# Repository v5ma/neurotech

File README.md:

Wiki
====

https://www.noisebridge.net/wiki/DreamTeam/Brainduinov2

Commands
========

Commands are sent by write ASCII characters to the bluetooth serial device. The brainduino echos back the lower-case compliment of the command sent 15 times followed by a return carridge. For example:

```
Client writes 'S' to bluetooth serial device
If the command is recieved by the brainduino, the brainduino writes 'sssssssssssssss' + '\r' back over bluetooth

```
ASCII | Result
---   | ---
I     | Bypass the MAX7480 (8th-order butterworth filter)
P     | Set 200HZ low-pass corner frequency of MAX7480 (8th-order butterworth filter)
O     | Set 150HZ low-pass corner frequency of MAX7480 (8th-order butterworth filter)
Q     | Set 100HZ low-pass corner frequency of MAX7480 (8th-order butterworth filter)
Z     | Set 50HZ low-pass corner frequency of MAX7480 (8th-order butterworth filter)
M     | Set 40HZ low-pass corner frequency of MAX7480 (8th-order butterworth filter)
S     | Set 32HZ low-pass corner frequency of MAX7480 (8th-order butterworth filter)
V     | Set sample rate to 500HZ
W     | Set sample rate to 250HZ
B     | Set sample rate to 190HZ
A     | Impedance check on with +1ch
T     | Impedance check on with -1ch
C     | Impedance check on with +2ch
D     | Impedance check on with -2ch
E     | Impedance check off
F     | Generate test signal with frequency = 12HZ
G     | Generate test signal with frequency = 28HZ
H     | Generate test signal with frequency = 111HZ
J     | Generate test signal with power = 0.1
K     | Generate test signal with power = 1
Y     | Set 4 channel mode
X     | Set 2 channel mode with 500HZ sample rate
U     | Set 2 channel mode with 250HZ sample rate

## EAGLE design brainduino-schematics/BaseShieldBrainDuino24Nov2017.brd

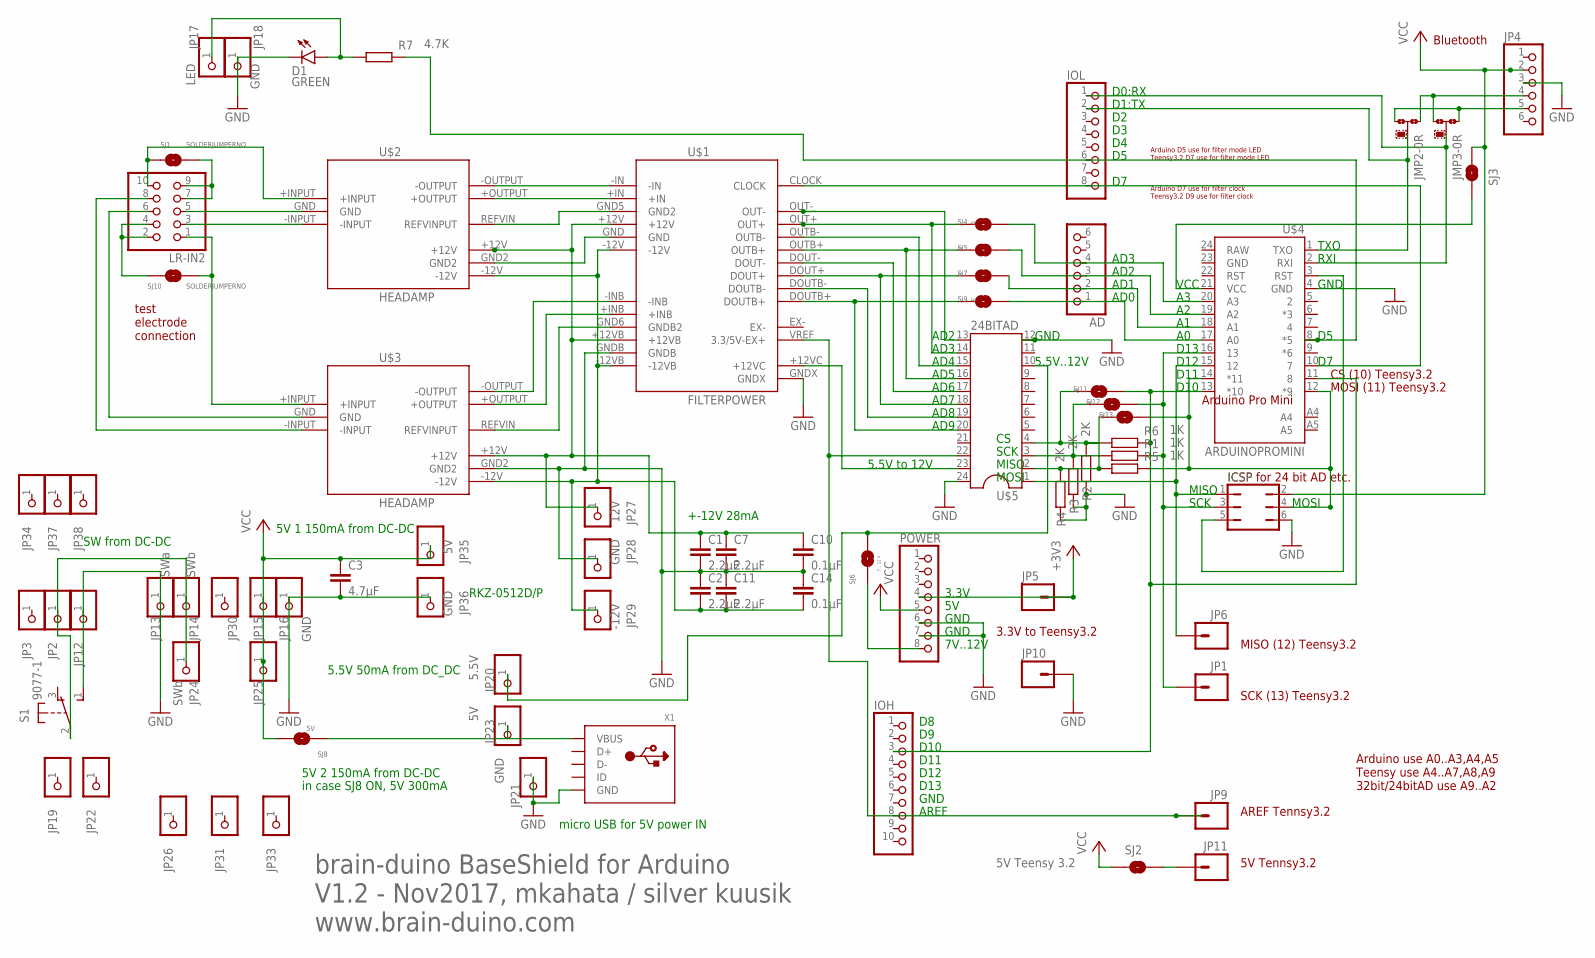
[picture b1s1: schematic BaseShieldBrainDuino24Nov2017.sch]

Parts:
AD: PINHD-1X6; 1X06
C1, C2, C7, C11: 2.2µF; C0402
C3: 4.7µF; C0402
C10, C14: 0.1µF; C0402
D1: GREEN; LED-0603
ICSP: JP3Q
IOH: PINHD-1X10; 1X10
IOL: PINHD-1X8; 1X08
JMP2: RX; A0R-JMP
JMP3: TX; A0R-JMP
JP1, JP5, JP6, JP9, JP10, JP11: M01PTH; 1X01
JP2, JP3, JP12, JP19, JP22, JP26, JP30, JP31, JP33, JP34, JP37, JP38: PINHD-1X1; 1X01
JP4: PINHD-1X6; 1X06
JP13: SWa; 1X01
JP14, JP24: SWb; 1X01
JP15, JP25: +5V; 1X01
JP16, JP18, JP21, JP28, JP36: GND; 1X01
JP17: LED; 1X01
JP20: 5.5V; 1X01
JP23, JP35: 5V; 1X01
JP27: 12V; 1X01
JP29: -12V; 1X01
LR-IN2: PINHD-2X5/90; 2X05/90
POWER: PINHD-1X8; 1X08
R1, R5, R6: 1K; R0402
R2, R3, R4: 2K; R0402
R7: 4.7K; R0402
S1: 9077-1
SJ1, SJ10: SOLDERJUMPERNO; SJ_2S-NO
SJ2: 5V Teensy 3.2; SJ_2S-NO
SJ3: 5V Arduino Pro Mini; SJ_2S-NO
SJ4: A5; SJ_2S-NO
SJ5, SJ11, SJ12, SJ13: A4; SJ_2S-NO
SJ6: 7 .. 12 V; SJ_2S-NO
SJ7: A2; SJ_2S-NO
SJ8: 5V; SJ_2S-NO
SJ9: A0; SJ_2S-NO
U$1: FILTERPOWER
U$2, U$3: HEADAMP
U$4: ARDUINOPROMINI
U$5: 24BITAD
X1: USB_MICRO_20329_V2; 4UCONN_20329_V2

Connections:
+3V3: JP5.1, POWER.4
+12VB: C1.1, C7.1, C10.1, JP27.1, U$1.+12V, U$1.+12VB, U$2.+12V, U$3.+12V
-12V: C2.2, C11.2, C14.2, JP29.1, U$1.-12V, U$1.-12VB, U$2.-12V, U$3.-12V
GND: C1.2, C2.1, C3.2, C7.2, C10.2, C11.1, C14.1, D1.C, ICSP.6, JP4.3, JP10.1, JP12.1, JP13.1, JP16.1, JP18.1, JP21.1, JP28.1, JP36.1, POWER.6, POWER.7, R2.1, R3.1, R4.1, S1.1 (S), U$1.GNDB, U$1.GNDX, U$3.GND2, U$4.4 (GND), U$5.12, U$5.24, X1.BASE@1 (GND), X1.BASE@2 (GND), X1.GND, X1.SPRT@1 (GND), X1.SPRT@2 (GND), X1.SPRT@3 (GND), X1.SPRT@4 (GND)
unnamed: SJ3.1, U$4.21 (VCC)
unnamed: U$1.GND, U$2.GND2
unnamed: JP2.1, JP14.1, JP24.1, S1.2
unnamed: POWER.8, SJ6.1
unnamed: ICSP.3, JP1.1, R1.2, SJ12.2, U$4.16 (13)
unnamed: LR-IN2.8, U$3.-INPUT
unnamed: JP23.1, SJ8.1, X1.VBUS
unnamed: U$1.GND6 (GNDB2), U$3.REFVIN (REFVINPUT)
unnamed: U$1.-INB, U$3.-OUTPUT
unnamed: U$1.+INB, U$3.+OUTPUT
unnamed: LR-IN2.3, U$2.-INPUT
unnamed: U$1.OUTB-, U$5.15
unnamed: U$1.+12VC, U$5.23
unnamed: U$1.OUT-, U$5.13
unnamed: JMP2.1, JMP3.3, JP4.4
unnamed: IOL.8, U$1.CLOCK, U$4.10 (7)
unnamed: ICSP.1, JP6.1, U$4.15 (12), U$5.1
unnamed: IOL.2, JMP2.2, U$4.1 (TXO)
unnamed: U$1.-IN, U$2.-OUTPUT
unnamed: IOL.1, JMP3.2, U$4.2 (RXI)
unnamed: IOH.3, R6.2, SJ11.2, U$4.11 (8), U$4.13 (*10)
unnamed: AD.2, SJ7.2, U$4.18 (A1)
unnamed: AD.1, SJ9.2, U$4.17 (A0)
unnamed: ICSP.4, R5.2, SJ13.2, U$4.12 (*9), U$4.14 (*11)
unnamed: JMP2.3, JMP3.1, JP4.5
unnamed: SJ9.1, U$1.DOUTB+, U$5.20
unnamed: JP11.1, SJ2.2
unnamed: JP20.1, SJ6.2, U$5.10
unnamed: U$1.DOUTB-, U$5.19
unnamed: U$1.+IN, U$2.+OUTPUT
unnamed: SJ7.1, U$1.DOUT+, U$5.18
unnamed: U$1.DOUT-, U$5.17
unnamed: IOH.8, JP9.1, U$1.VREF (3.3/5V-EX+), U$5.22
unnamed: AD.4, SJ4.2, U$4.20 (A3)
unnamed: SJ4.1, U$1.OUT+, U$5.14
unnamed: SJ5.1, U$1.OUTB+, U$5.16
unnamed: LR-IN2.1, SJ10.2, U$3.+INPUT
unnamed: LR-IN2.10, SJ1.1, U$2.+INPUT
unnamed: LR-IN2.7, LR-IN2.9, SJ1.2
unnamed: LR-IN2.2, LR-IN2.4, SJ10.1
unnamed: R2.2, R6.1, SJ11.1, U$5.4
unnamed: R1.1, R3.2, SJ12.1, U$5.3
unnamed: R4.2, R5.1, SJ13.1, U$5.2
unnamed: AD.3, SJ5.2, U$4.19 (A2)
unnamed: U$1.GND5 (GND2), U$2.REFVIN (REFVINPUT)
unnamed: LR-IN2.6, U$3.GND
unnamed: ICSP.5, U$4.3 (RST)
unnamed: D1.A, JP17.1, R7.1
unnamed: IOL.6, R7.2, U$4.8 (*5)
unnamed: LR-IN2.5, U$2.GND
VCC: C3.1, ICSP.2, JP4.2, JP15.1, JP25.1, JP35.1, POWER.5, SJ2.1, SJ3.2, SJ8.2

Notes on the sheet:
D0:RX
D1:TX
D13
D12
AREF
GND
AD0
AD1
AD2
AD3
7V..12V
D10
D11
test electrode connection
MOSI (11) Teensy3.2
brain-duino BaseShield for Arduino V1.2 - Nov2017, mkahata / silver kuusik www.brain-duino.com
Bluetooth
MOSI
MISO
SCK
3.3V to Teensy3.2
SCK (13) Teensy3.2
MISO (12) Teensy3.2
ICSP for 24 bit AD etc.
CS (10) Teensy3.2
Arduino use A0..A3,A4,A5 Teensy use A4..A7,A8,A9 32bit/24bitAD use A9..A2
5V Tennsy3.2
Arduino D7 use for filter clock Teensy3.2 D9 use for filter clock
3.3V
AD9
AD8
AD7
AD6
AD5
AD4
5.5V..12V
AREF Tennsy3.2
TXO
RXI
VCC

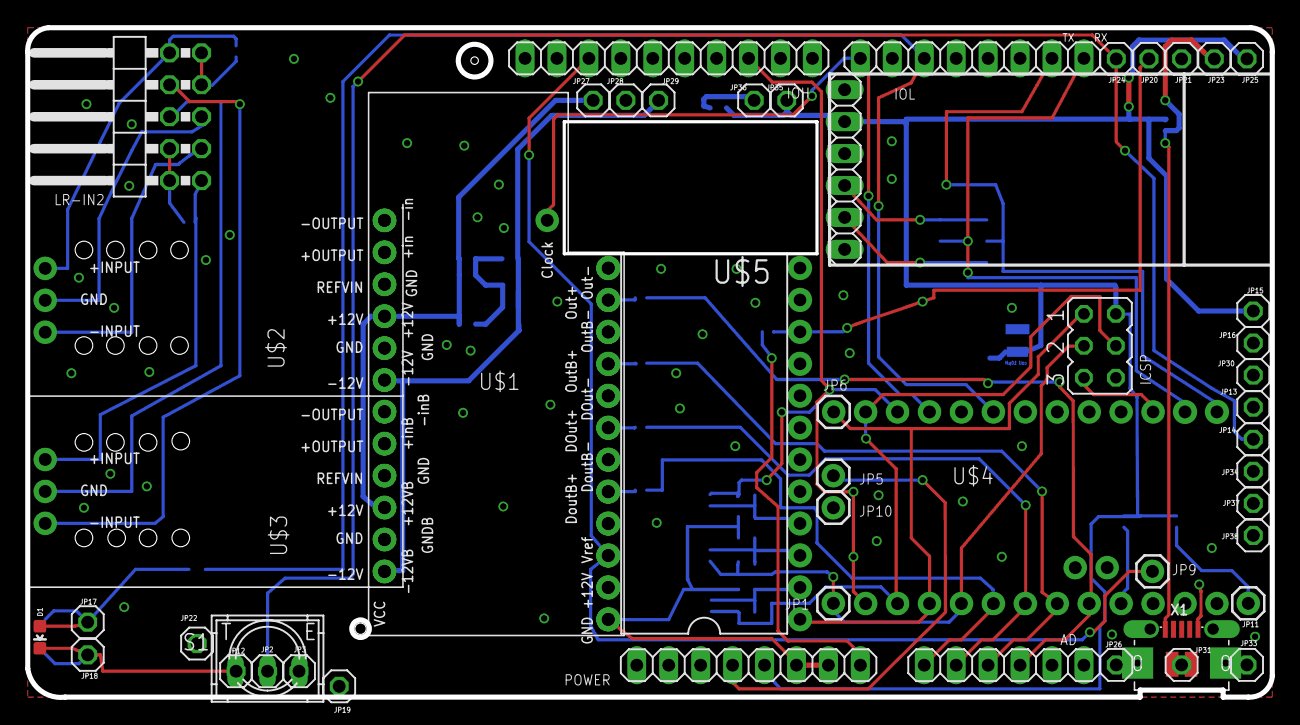
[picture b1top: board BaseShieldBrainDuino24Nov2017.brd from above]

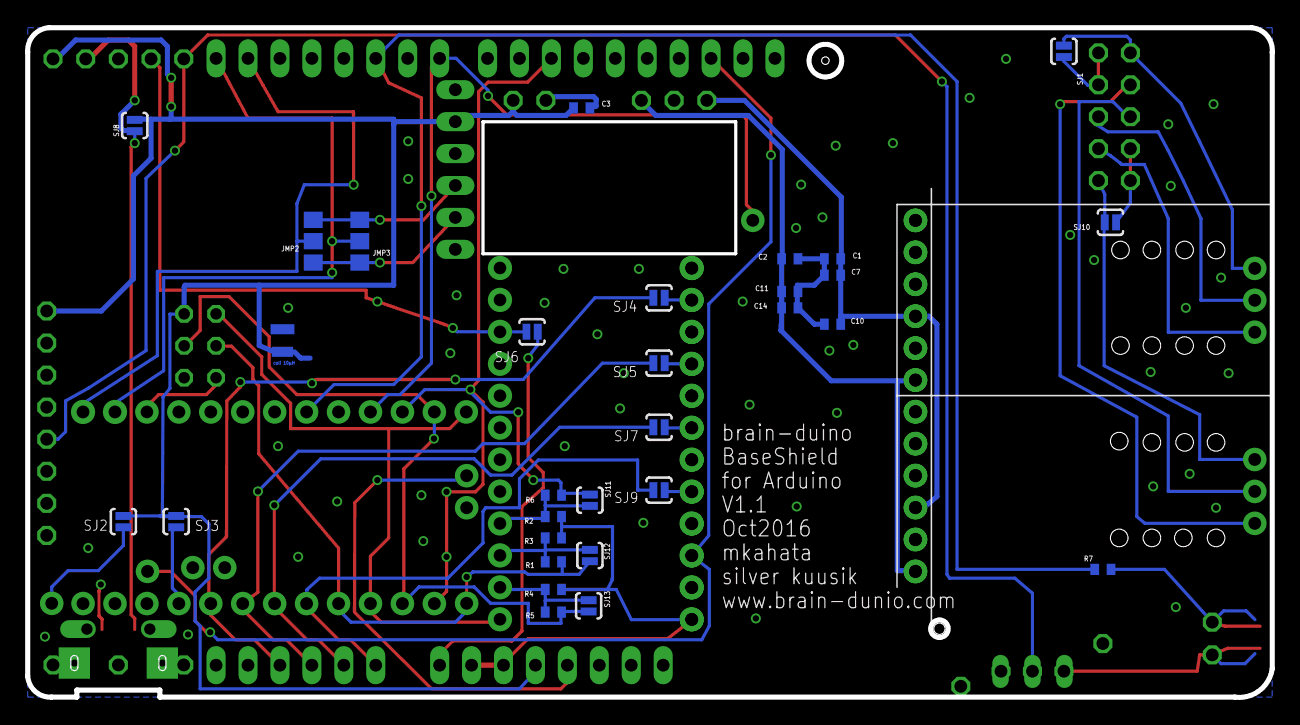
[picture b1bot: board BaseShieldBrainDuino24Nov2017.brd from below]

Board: 2 copper layers, 99.0 x 53.3 mm, 78 parts (29 on the bottom side), 55 nets.

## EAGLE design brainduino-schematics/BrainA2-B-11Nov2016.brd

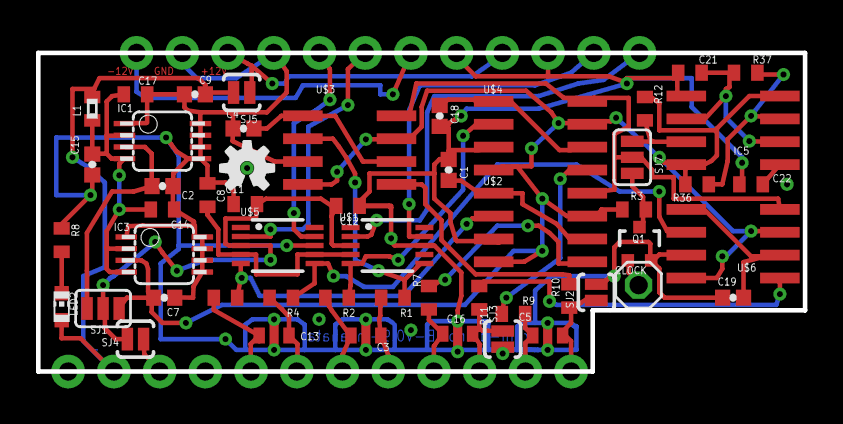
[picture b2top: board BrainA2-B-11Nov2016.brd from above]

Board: 2 copper layers, 42.6 x 17.7 mm, 55 parts (0 on the bottom side), 42 nets.

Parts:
C1, C4, C18, C19: 0.1µF; 0402-CAP
C2, C7: 4.7µF; 0402-CAP
C3, C5, C13, C16: C0603
C8, C11, C12, C14, C17: 2.2uF; C0402
C9, C15: 2.2µF; 0402-CAP
C21: 2.2nF; C0402
C22: 0.1µF; C0402
CLOCK: 1X01
FRAME1: FRAME-LETTER; CREATIVE_COMMONS
IC1: ADP1720ARMZ-3.3; MSOP08
IC3: ADP1720ARMZ-5; MSOP08
IC5: TLC555CDR; SO08
JP1, JP2: 1X12_NO_SILK
L1: BLM15HB121SN1; 0402
LED2: CHIP-LED0603
Q1: MOSFET-NCHANNEL2N7002PW; SOT323
R1, R2, R4, R5: 4.7K; R0402
R3: 10k; R0402
R7, R9, R10, R11: 470; R0402
R8: 20k; R0402
R12: 10K; R0402
R36: 1K; R0402
R37: 100K; R0402
SJ1, SJ7: SJ_3
SJ2, SJ3, SJ4, SJ5: SOLDERJUMPERNO; SJ_2S-NO
U$1, U$5: AD8475; MSOP10
U$2, U$3, U$4, U$6: MAX7480ESA+; MAX7480
U$8: OSHW-LOGO-S

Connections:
5V: C7.1, IC3.3, IC5.4, IC5.8, R3.2, R12.2, R36.2, SJ1.1, U$2.4, U$2.7, U$3.4, U$3.7, U$4.4, U$4.7, U$6.4, U$6.7
+12V: JP2.4, JP2.10, SJ5.1
-12V: JP2.6, JP2.12
GND: C1.1, C2.1, C3.GND, C4.1, C5.GND, C7.2, C8.1, C9.1, C11.1, C12.1, C13.GND, C14.1, C15.1, C16.GND, C17.1, C18.1, C19.1, C21.1, C22.1, IC1.1, IC1.5, IC1.6, IC1.7, IC1.8, IC3.1, IC3.5, IC3.6, IC3.7, IC3.8, IC5.1, JP1.12, JP2.3, JP2.5, JP2.9, JP2.11, Q1.2, R8.2, SJ2.2, SJ3.2, U$1.8, U$2.3, U$3.3, U$4.3, U$5.8, U$6.3
unnamed: C13.2, JP1.8, R5.2
unnamed: C1.2, U$2.1, U$2.6
unnamed: R11.1, U$6.5
unnamed: JP2.1, U$1.2
unnamed: R7.1, U$2.5
unnamed: JP2.2, U$1.9
unnamed: C3.2, JP1.6, R2.2
unnamed: C3.1, JP1.5, R1.2
unnamed: C5.2, JP1.1, R10.2, SJ2.1
unnamed: R2.1, U$1.5, U$4.2
unnamed: C4.2, U$3.1, U$3.6
unnamed: Q1.3, R3.1, SJ7.3
unnamed: JP1.10, SJ4.1
unnamed: R10.1, U$3.5
unnamed: C8.2, U$1.4, U$5.4
unnamed: LED2.C, R8.1
unnamed: R4.1, U$5.6, U$6.2
unnamed: JP2.8, U$5.9
unnamed: C13.1, JP1.7, R4.2
unnamed: JP2.7, U$5.2
unnamed: C5.1, JP1.2, R9.2
unnamed: C18.2, U$4.1, U$4.6
unnamed: C14.2, C15.2, C17.2, IC1.2, IC1.4, IC3.2, IC3.4, L1.2
unnamed: R9.1, U$4.5
unnamed: CLOCK.1, Q1.1
unnamed: R5.1, U$2.2, U$5.5
unnamed: R1.1, U$1.6, U$3.2
unnamed: IC5.3, R12.1, SJ7.1
unnamed: C16.1, JP1.4, R7.2
unnamed: C2.2, IC1.3, SJ1.3
unnamed: C16.2, JP1.3, R11.2, SJ3.1
unnamed: C19.2, U$6.1, U$6.6
unnamed: SJ7.2, U$2.8, U$3.8, U$4.8, U$6.8
unnamed: IC5.7, R36.1, R37.2
unnamed: C21.2, IC5.2, IC5.6, R37.1
unnamed: C22.2, IC5.5
V+: C9.2, JP1.11, L1.1, LED2.A, SJ5.2
VCCIO: C11.2, C12.2, SJ1.2, SJ4.2, U$1.3, U$5.3

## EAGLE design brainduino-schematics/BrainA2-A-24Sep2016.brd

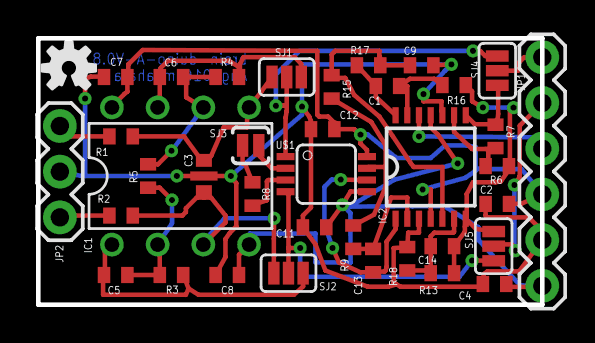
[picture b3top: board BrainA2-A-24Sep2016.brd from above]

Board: 2 copper layers, 28.0 x 14.8 mm, 38 parts (0 on the bottom side), 29 nets.

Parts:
C1, C13: 1µF; C0402
C2, C4: 2.2µF; C0402
C3: X2Y; C0603
C5, C6: 4700pF; C0402
C7, C8, C11, C12: 0.1µF; C0402
C9, C14: 47pF; C0402
IC1: OPA2111KP; DIL08
IC2: OP4177; TSSOP14
JP1: 1X06
JP2: 1X03
LOGO1: OSHW-LOGOS; OSHW-LOGO-S
R1, R2: 4.7K; R0402
R3, R4, R6, R7: 100K; R0402
R5: 2K; R0402
R8: 200; R0402
R9, R13, R16, R17: 1M; R0402
R15, R18: 4.02K; R0402
SJ1, SJ2, SJ4, SJ5: SJ_3_PASTE2&3
SJ3: SOLDERJUMPERNO; SJ_2S-NO
U$1: AD8422ARMZ; AD8220

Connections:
GND: C2.1, C3.GND, C4.2, C7.1, C8.2, C9.1, C11.2, C12.1, IC2.3, IC2.10, JP1.2, JP2.2, R18.2
unnamed: JP2.3, R1.1
unnamed: R8.2, SJ3.1
unnamed: JP2.1, R2.1
unnamed: C3.2, IC1.3, R2.2, SJ2.1
unnamed: C3.1, IC1.5, R1.2, SJ1.1
unnamed: IC2.9, R6.1, R7.2
unnamed: C5.1, IC1.2, R3.1, R5.2
unnamed: C6.1, IC1.6, R4.1, R5.1
unnamed: SJ1.2, SJ4.1, U$1.1
unnamed: SJ2.2, SJ5.1, U$1.4
unnamed: C5.2, IC1.1, R3.2, SJ2.3
unnamed: C6.2, IC1.7, R4.2, SJ1.3
unnamed: R8.1, U$1.3
unnamed: JP1.6, SJ4.2
unnamed: C1.2, IC2.13, R16.2
unnamed: SJ3.2, U$1.2
unnamed: C9.2, IC2.5, R15.1, R17.2
unnamed: R9.2, R15.2, U$1.7
unnamed: C13.2, IC2.2, R9.1
unnamed: C14.2, IC2.7, R6.2, R13.1, R16.1, SJ5.3
unnamed: C13.1, IC2.1, U$1.6
unnamed: C14.1, IC2.6, R13.2, R18.1
unnamed: IC2.12, JP1.4
unnamed: C1.1, IC2.14, R17.1
unnamed: IC2.8, R7.1, SJ4.3
unnamed: JP1.5, SJ5.2
V+: C2.2, C7.2, C12.2, IC1.8, IC2.4, JP1.3, U$1.8
V-: C4.1, C8.1, C11.1, IC1.4, IC2.11, JP1.1, U$1.5

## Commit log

2018-07-07 Add output
2018-07-07 Add other files
2018-07-07 Create Aframe code
2018-07-26 sync local changes + python code for brain data over web sockets
2018-07-29 improve path finding to brainduino device
2018-08-02 working(ish) enhancements to python server
2018-08-10 Create nodejs server and enable the python client to send brainduino messages into it
2018-08-16 Create webxrexperiment2
2018-08-16 Create x
2018-08-16 Cleaning directories
2018-08-16 Revert "Merge remote-tracking branch 'Micah1/brainduino-web-ui'"
    This reverts commit e79a4c6e3b188e2015a6ba0393e4bb493e4bd392, reversing
    changes made to 2e5f3e073e04b37a0dffcbbef3c83062ce5d8c1b.
2018-09-20 Merging repos
2018-09-20 intro fft
2018-09-24 Refactor with go-broadcast in Device
2018-09-27 breakout webstuff and mathstuff from main
2018-09-27 Refactor Device into a Subscriber
2018-09-27 write commands to the brainduino over http
2018-09-27 safe retrieval of data from chans array
2018-09-30 added chartsngraphs
2018-09-30 a little documentation
2018-09-30 need root path to index
2018-10-04 autoscale y-axis for timeseries charts
2018-10-11 use brainduinopath
2018-10-18 undersea scene w/ fft
2018-10-25 3d scatter plot spectrogram
2018-10-25 increase frequency of fft
2018-10-28 breaking out
2018-10-28 end-to-end successful from www
2018-11-04 use iris logger on server
2018-11-08 new stuff
2018-11-10 refactor the scatterplot towards having multiple in the same VR experience
2018-11-10 remove go Emit hack
2018-11-18 registration api and html templating
2018-12-01 <now you can click to rotate the scatterplot>
2018-12-18 Rename index.html to indexrotateplot.html
2018-12-18 Rename index.html to index18Nov2018.html
2018-12-20 allow internal and external address when starting
2019-01-10 audiogit add . --all
2019-01-12 <new text editor that helps with debugging javascript etc, type code in terminal to run it, added a function to the audio so that you can start audio in the webbrowser by pressing the letter k, added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
2019-01-13 <you can turn left/right in VR by pressing left/right on the controller, there is a VR Console Log to help people figure out the controls inside VR. I changed it from cubes to planes and it feels mor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
2019-01-13 <adding a backup of leftrightconsole which contains a bunch of upgrades>
2019-01-31 <audio updates>
2019-01-31 progress towards a more flexible audio interface
2019-02-28 prettify index.html!

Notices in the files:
parts and their libraries:
SparkFun-Connectors: Licensing: Creative Commons ShareAlike 4.0 International - https://creativecommons.org/licenses/by-sa/4.0
SparkFun-Aesthetics: Released under the Creative Commons Attribution Share-Alike 4.0 License
SparkFun-Aesthetics: https://creativecommons.org/licenses/by-sa/4.0
